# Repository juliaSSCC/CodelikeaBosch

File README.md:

# Code #LikeABosch
## Features

### ESP32 based

* ESP32-WROOM-32D Microcontroller 
* Deep sleep mode (10uA)

### Smart position tracking

* BLE to better track postion
    * RSSI tracker for postion

### Smart temperature management

* Base temperature for each room
* Comfort temperature for each room

### Smart lighting

* Turn lights off in empty rooms
* LDR to measure light level
    * Three sensosrs to better capture the whole ambient

### Zigbee Transceiver

* Low power
* Deep Sleep mode (0.02uA)

### Supervisory system

* Shows current temperature
* Shows target temperature
* Shows ocupation
* Light level
* To be integrated to HA

### Power Supply

* Battery powered 3x(AAA)
* Buck converter (3.3V and 1.8V)

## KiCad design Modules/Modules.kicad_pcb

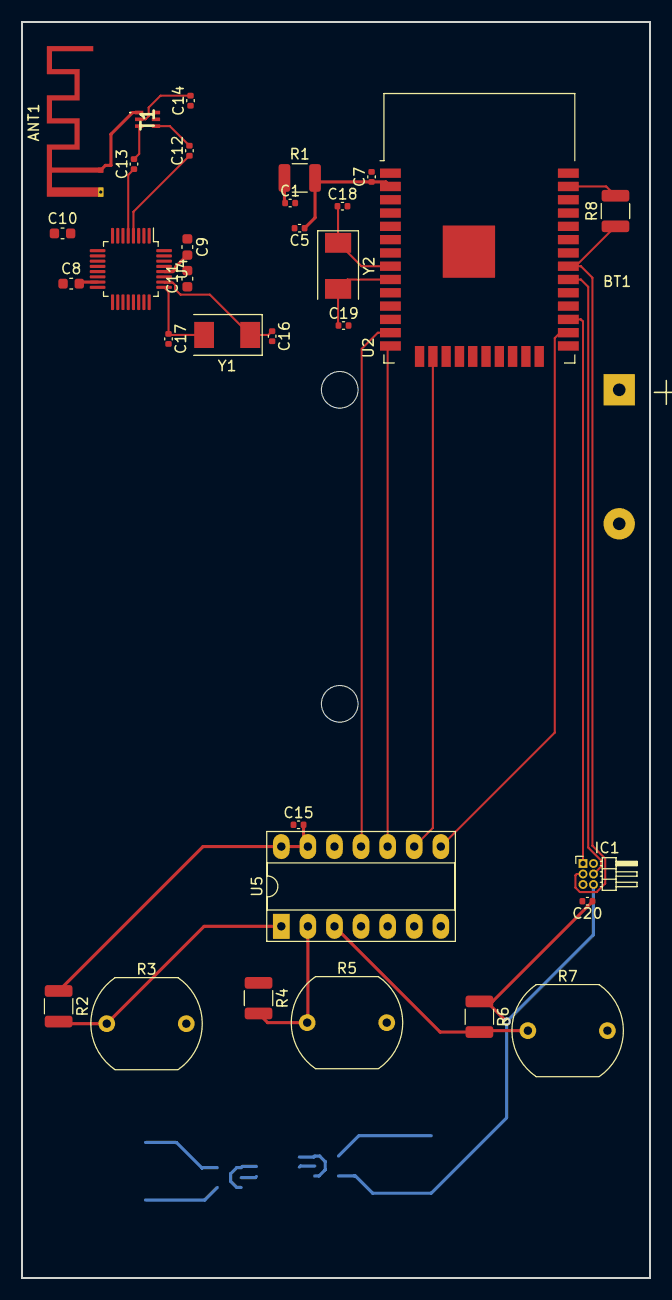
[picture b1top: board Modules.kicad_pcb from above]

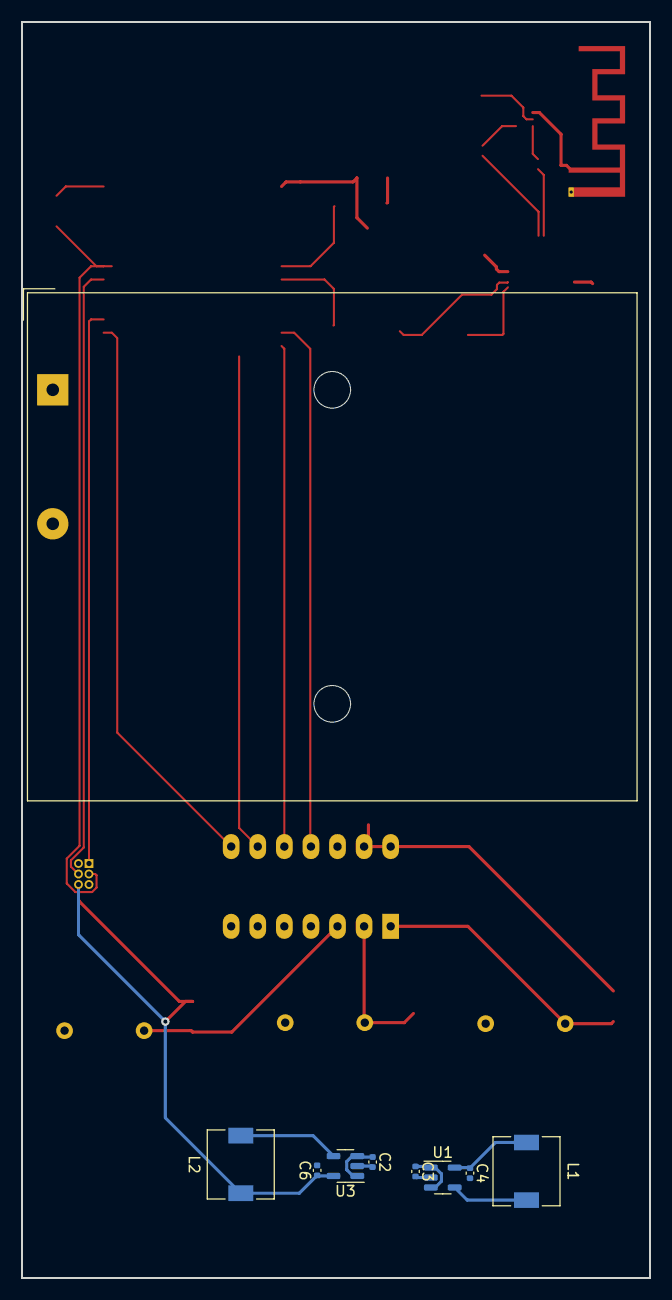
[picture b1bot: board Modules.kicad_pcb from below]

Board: 2 copper layers, 60.0 x 120.0 mm, 41 parts (9 on the bottom side), 36 nets.

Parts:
ANT1: SWRA117D; Texas_SWRA117D_2.4GHz_Right
BT1: Battery; BatteryHolder_TruPower_BH-331P_3xAA
C1, C15: 1u; C_0402_1005Metric
C2, C3: 4.7u; C_0402_1005Metric
C4, C5, C6: 10u; C_0402_1005Metric
C7: .1u; C_0402_1005Metric
C8, C9: 1u; C_0603_1608Metric
C10, C11: 100n; C_0603_1608Metric
C12, C13, C14: 22p; C_0402_1005Metric
C16, C17, C18, C19: 12p; C_0402_1005Metric
C20: 0.1u; C_0402_1005Metric
IC1: TMP126NDCKR; PinHeader_2x03_P1.00mm_Horizontal
L1, L2: 10u; L_6.3x6.3_H3
R1, R8: 10k; R_1210_3225Metric
R2, R4, R6: 330k; R_1210_3225Metric
R3, R5, R7: LDR03; R_LDR_10x8.5mm_P7.6mm_Vertical
T1: 2450FB15L0001E
U1: TPS62202DBV; SOT-23-5
U2: ESP32-WROOM-32D; ESP32-WROOM-32
U3: TPS62203DBV; SOT-23-5
U4: AT86RF233-ZU; LQFP-32_5x5mm_P0.5mm
U5: MCP3204; DIP-14_W7.62mm_Socket_LongPads
Y1: 16M; Crystal_SMD_0603-2Pin_6.0x3.5mm
Y2: 40M; Crystal_SMD_0603-2Pin_6.0x3.5mm

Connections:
+1V8: C4.1, C8.2, C9.2, L1.1, U1.5 (SW), U4.15 (DEVDD), U4.28 (EVDD)
+3V3: C5.1, C6.1, C7.1, C15.2, C20.1, IC1.6 (VDD), L2.1, R1.2, R2.1, R4.1, R6.1, U2.2 (VDD), U3.5 (SW), U5.13 (Vref), U5.14 (Vdd)
DEEP_SLEEP: U2.33 (IO21), U4.11 (SLP_TR)
GND: ANT1.2 (GND), C1.2, C5.2, C7.2, C8.1, C9.1, C10.1, C11.1, C14.1, C15.1, C16.2, C17.2, C18.2, C19.2, C20.2, IC1.5 (~ALERT), T1.5 (GND_1), T1.6 (GND_2), U2.1 (GND), U2.15 (GND), U2.38 (GND), U2.39 (GND), U4.3 (AVSS), U4.6 (AVSS), U4.7 (DVSS), U4.12 (DVSS), U4.16 (DVSS), U4.18 (DVSS), U4.21 (DVSS), U4.27 (AVSS), U4.30 (AVSS), U4.31 (AVSS), U4.32 (AVSS), U5.4 (CH3), U5.7 (DGND)
GNDA: IC1.2 (GND), R3.2, R5.2, R7.2, U5.12 (AGND)
HSPI_MISO: U2.14 (IO12), U4.20 (MISO), U5.10 (Dout)
HSPI_MOSI: U2.16 (IO13), U4.22 (MOSI), U5.9 (Din)
HSPI_SCK: U2.13 (IO14), U4.19 (SCLK), U5.11 (CLK)
LDR1: R2.2, R3.1, U5.1 (CH0)
LDR2: R4.2, R5.1, U5.2 (CH1)
LDR3: R6.2, R7.1, U5.3 (CH2)
LDR_CS: U2.26 (IO4), U5.8 (~CS/SHDN)
unnamed: ANT1.1 (SIG), T1.1 (UNBALANCED_PORT)
unnamed: BT1.1 (+), C2.1, C3.1, U1.1 (VI), U1.3 (EN), U3.1 (VI), U3.3 (EN)
unnamed: BT1.2 (-), C2.2, C3.2, C4.2, C6.2, U1.2 (GND), U3.2 (GND)
unnamed: C1.1, R1.1, U2.3 (EN)
unnamed: C10.2, U4.13 (DVDD), U4.14 (DVDD)
unnamed: C11.2, U4.29 (AVDD)
unnamed: C12.1, U4.4 (RFP)
unnamed: C13.1, U4.5 (RFN)
unnamed: C14.2, T1.2 (DC_FEED_+_RF_GND)
unnamed: L1.2, U1.4 (FB)
unnamed: L2.2, U3.4 (FB)
unnamed: U4.1 (DIG3), U4.2 (DIG4), U4.9 (DIG1), U4.10 (DIG2)
RFN: C13.2, T1.3 (BALANCED_PORT_1)
RFP: C12.2, T1.4 (BALANCED_PORT_2)
RF_CS: U2.28 (IO17), U4.23 (~SEL)
RST: U2.36 (IO22), U4.8 (~RST)
TEMP_CS: IC1.1 (~CS), U2.27 (IO16)
VSPI_MISO: IC1.3 (SIO), R8.1, U2.31 (IO19)
VSPI_MOSI: R8.2, U2.37 (IO23)
VSPI_SCK: IC1.4 (SCLK), U2.30 (IO18)
XTAL1: C18.1, U2.8 (IO32), Y2.1
XTAL1_RF: C16.1, U4.26 (XTAL1), Y1.1
XTAL2: C19.1, U2.9 (IO33), Y2.2
XTAL2_RF: C17.1, U4.25 (XTAL2), Y1.2

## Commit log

2022-09-30 Fixed README
2022-10-01 Added datasheets
2022-10-01 Added schematic and layout prototype
2022-10-02 First concept of the routed board
2022-10-02 added base documantation
2022-10-02 added temp sensor datasheet
2022-10-02 Added pricing calculation
2022-10-02 added esp datasheet
2022-10-02 final
2022-10-02 submission
